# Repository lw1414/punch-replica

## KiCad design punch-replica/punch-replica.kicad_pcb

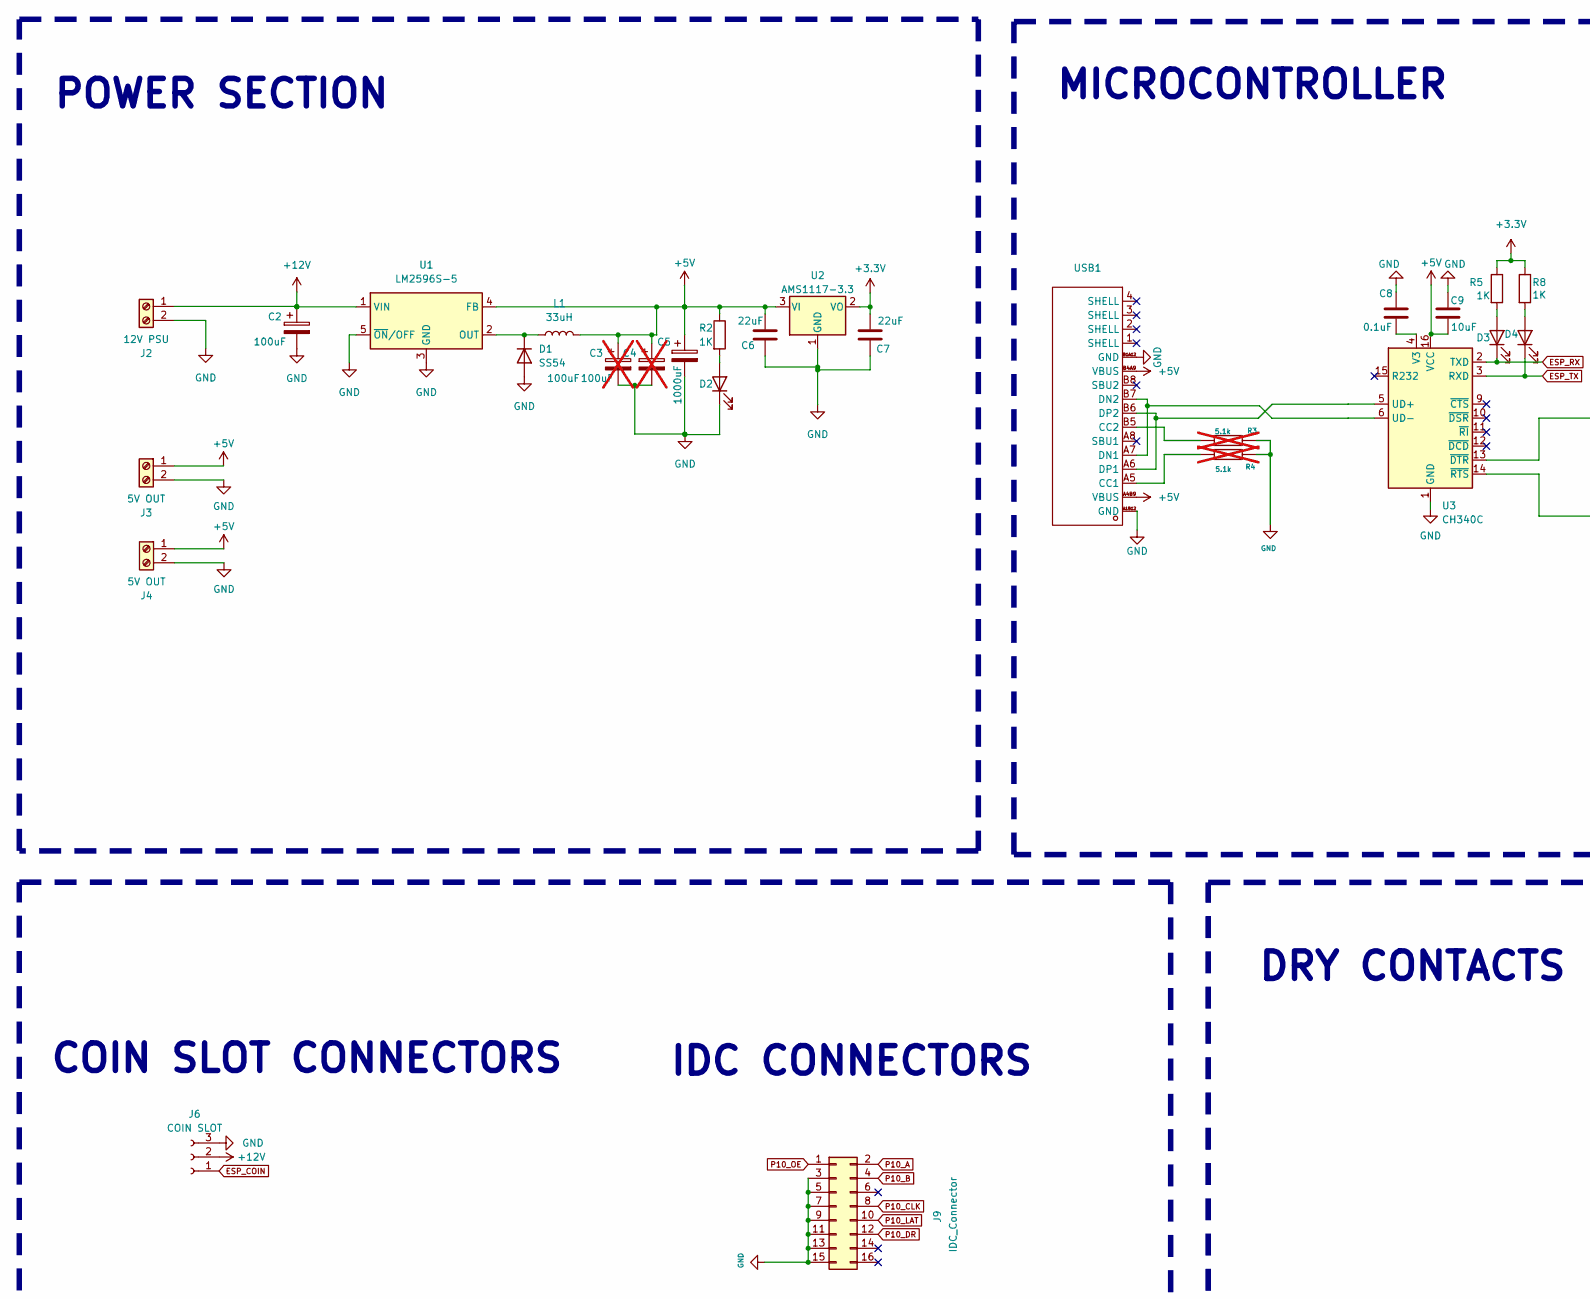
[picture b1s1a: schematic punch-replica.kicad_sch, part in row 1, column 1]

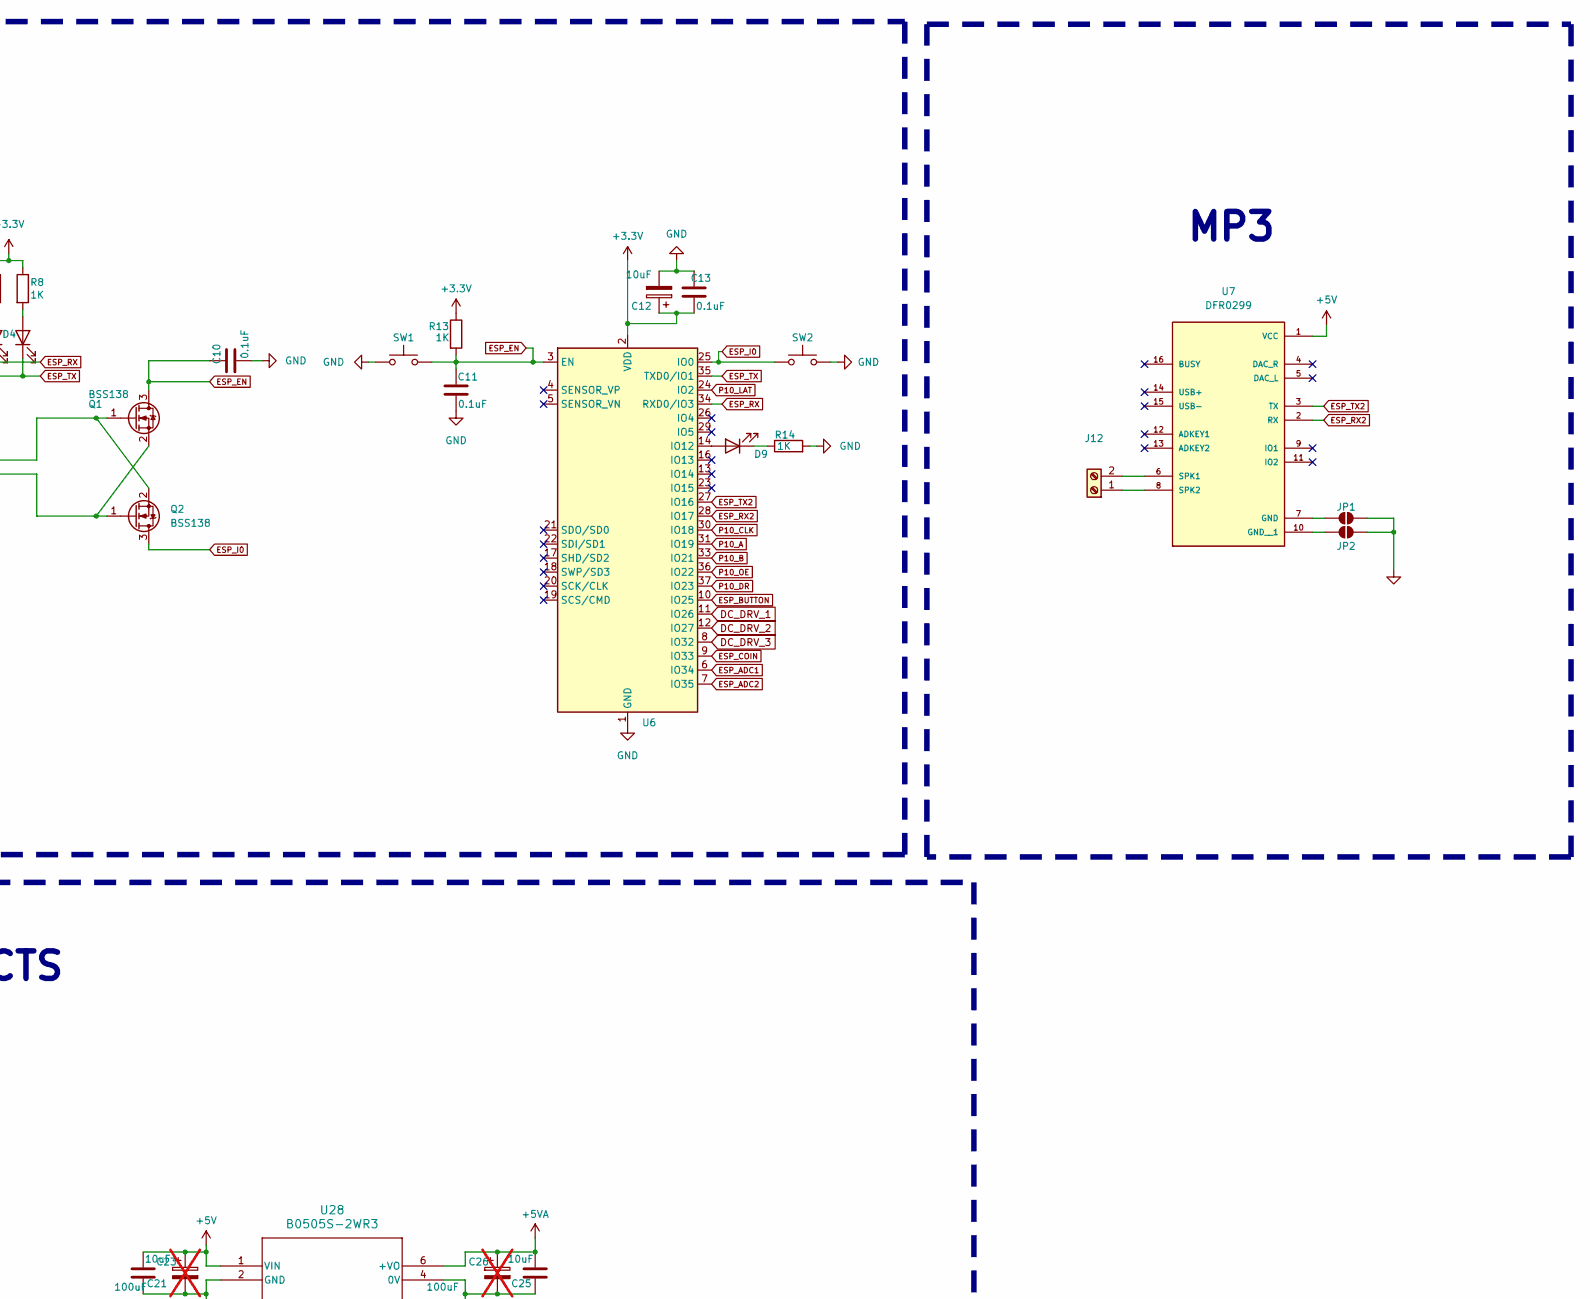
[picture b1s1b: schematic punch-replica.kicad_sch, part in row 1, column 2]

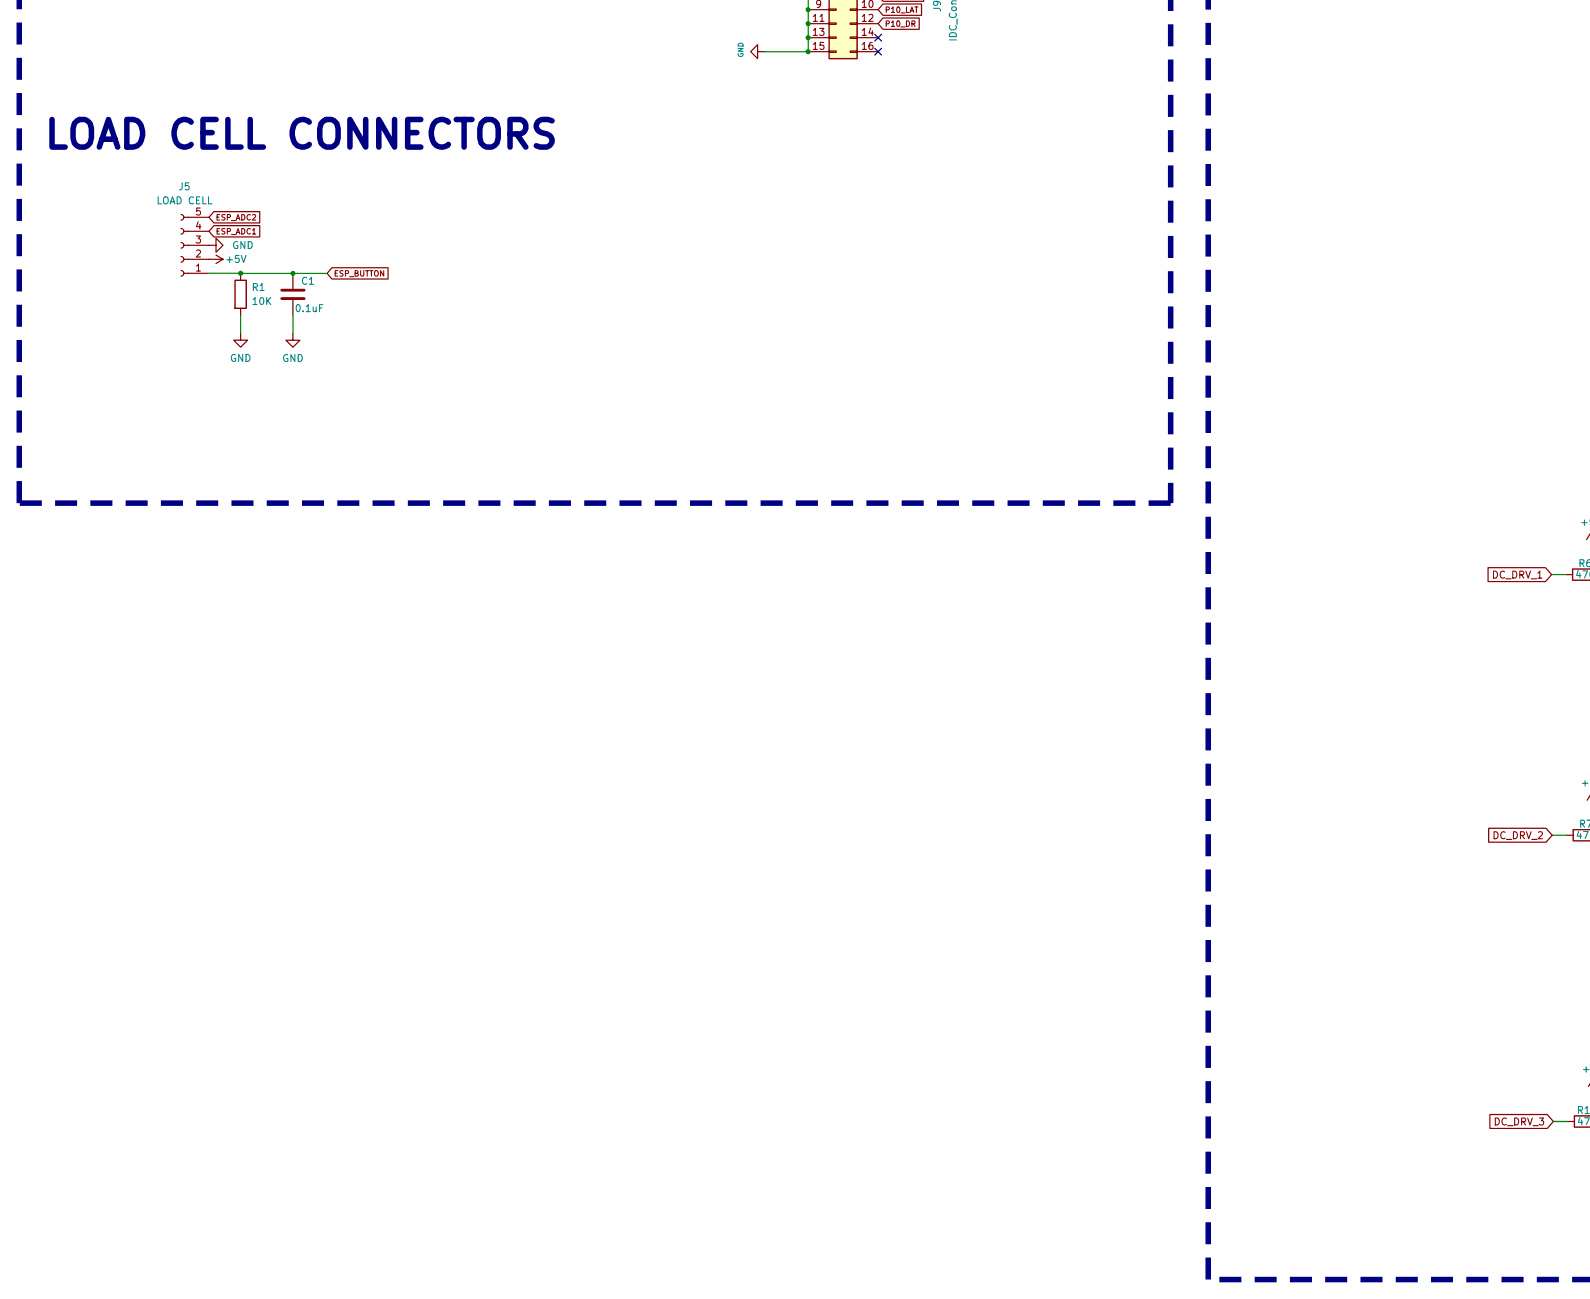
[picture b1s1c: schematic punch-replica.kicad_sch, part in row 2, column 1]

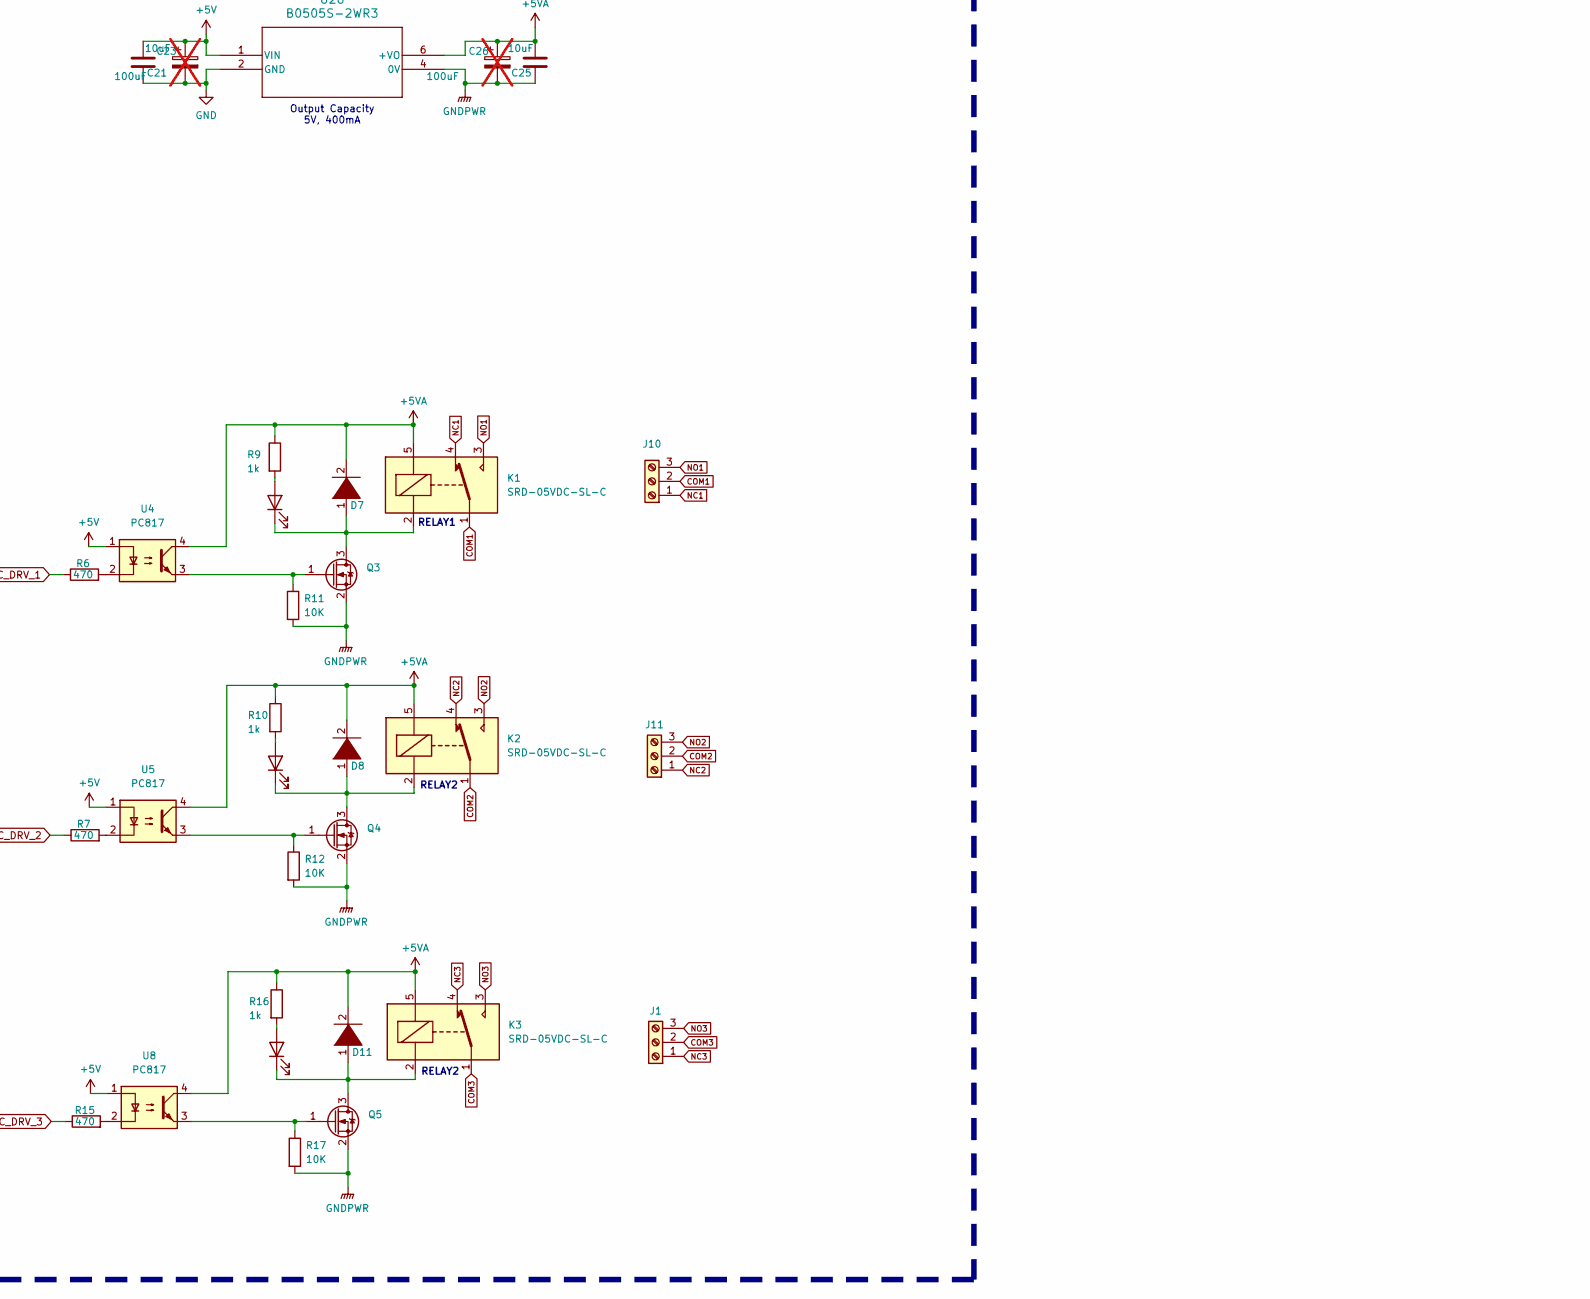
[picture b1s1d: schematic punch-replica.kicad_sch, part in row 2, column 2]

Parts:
C1, C8, C10, C11, C13: 0.1uF; C_0805_2012Metric_Pad1.18x1.45mm_HandSolder; LCSC C49678
C2: 100uF; C_Elec_10x10.2; LCSC C28241
C3, C4, C23, C26: 100uF; C_1210_3225Metric_Pad1.33x2.70mm_HandSolder; LCSC C394395; not fitted
C5: 1000uF; C_Elec_10x10.2; LCSC C189257
C6, C7: 22uF; C_0603_1608Metric; LCSC C59461
C9, C12, C21, C25: 10uF; C_0805_2012Metric_Pad1.18x1.45mm_HandSolder; LCSC C15850
D1: SS54; D_SMA; LCSC C22452
D2, D3, D4, D5, D6, D9, D10: LED; LED_0805_2012Metric_Pad1.15x1.40mm_HandSolder; LCSC C2297
D7, D8, D11: 1N4001; D_SOD-123F; LCSC C2892326
J1, J10, J11: Screw_Terminal_01x03; TerminalBlock_Phoenix_MKDS-1,5-3_1x03_P5.00mm_Horizontal
J2: 12V PSU; TerminalBlock_MaiXu_MX126-5.0-02P_1x02_P5.00mm
J3, J4: 5V OUT; TerminalBlock_MaiXu_MX126-5.0-02P_1x02_P5.00mm
J5: LOAD CELL; TerminalBlock_Phoenix_MKDS-1,5-5-5.08_1x05_P5.08mm_Horizont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
J6: COIN SLOT; TerminalBlock_Phoenix_MKDS-1,5-3_1x03_P5.00mm_Horizontal
J9: IDC_Connector; IDC-TH_16P-P2.54_C3406
J12: Screw_Terminal_01x02; TerminalBlock_MaiXu_MX126-5.0-02P_1x02_P5.00mm
JP1, JP2: SolderJumper_2_Open; SolderJumper-2_P1.3mm_Open_RoundedPad1.0x1.5mm
K1, K2, K3: SRD-05VDC-SL-C; Relay_SPDT_SANYOU_SRD_Series_Form_C; LCSC C35449
L1: 33uH; 470; LCSC C475918
Q1, Q2: BSS138; SOT-23; LCSC C426569
Q3, Q4, Q5: Q_NMOS_Depletion_GSD; SOT-23-3; LCSC C75882
R1, R11, R12, R17: 10K; R_0603_1608Metric_Pad0.98x0.95mm_HandSolder; LCSC C25804
R2, R5, R8, R13, R14: 1K; R_0603_1608Metric_Pad0.98x0.95mm_HandSolder; LCSC C21190
R3, R4: 5.1k; R_0603_1608Metric_Pad0.98x0.95mm_HandSolder; LCSC C103079; not fitted
R6, R7, R15: 470; R_0603_1608Metric_Pad0.98x0.95mm_HandSolder; LCSC C25210
R9, R10, R16: 1k; R_0603_1608Metric_Pad0.98x0.95mm_HandSolder; LCSC C21190
SW1, SW2: SW_Push; SW_Tactile_SPST_NO_Straight_CK_PTS636Sx25SMTRLFS; LCSC C2689642
U1: LM2596S-5; TO-263-5_TabPin3; LCSC C347421
U2: AMS1117-3.3; SOT-223-3_TabPin2; LCSC C5199435
U3: CH340C; SOP-16_3.9x9.9mm_P1.27mm; LCSC C84681
U4, U5, U8: PC817; APC-817xx-SL_AMB; LCSC C66405
U6: ESP32-WROOM-32; ESP32-WROOM-32U; LCSC C529577
U7: DFR0299; MODULE_DFR0299
U28: B0505S-2WR3; B_S-2WR2_MNS; LCSC C5369473
USB1: USB-C-SMD_TYPE-C16PIN; Manufacturer Part TYPE-C16PIN; LCSC Part Name Type-C 母 卧贴

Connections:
+3.3V: C7.2, C12.1, C13.1, R5.1, R8.1, R13.1, U2.2 (VO), U6.2 (VDD)
+5V: C3.1, C4.1, C5.1, C6.2, C9.1, C21.2, C23.1, J3.1, J4.1, J5.2, L1.2, R2.1, U1.4 (FB), U2.3 (VI), U3.16 (VCC), U4.1, U5.1, U7.1 (VCC), U8.1, U28.1 (VIN), USB1.A4B9 (VBUS), USB1.B4A9 (VBUS)
+5VA: C25.2, C26.1, D7.2 (A), D8.2 (A), D11.2 (A), K1.5, K2.5, K3.5, R9.1, R10.1, R16.1, U4.4, U5.4, U8.4, U28.6 (+VO)
+12V: C2.1, J2.1, J6.2, U1.1 (VIN)
COM1: J10.2, K1.1
COM2: J11.2, K2.1
COM3: J1.2, K3.1
DC_DRV_1: R6.1, U6.11 (IO26)
DC_DRV_2: R7.1, U6.12 (IO27)
DC_DRV_3: R15.1, U6.8 (IO32)
ESP_ADC1: J5.4, U6.6 (IO34)
ESP_ADC2: J5.5, U6.7 (IO35)
ESP_BUTTON: C1.2, J5.1, R1.1, U6.10 (IO25)
ESP_COIN: J6.1, U6.9 (IO33)
ESP_EN: C10.2, C11.2, Q1.3 (D), R13.2, SW1.2, U6.3 (EN)
ESP_I0: Q2.3 (D), SW2.1, U6.25 (IO0)
ESP_RX: D3.1 (K), U3.2 (TXD), U6.34 (RXD0/IO3)
ESP_RX2: U6.28 (IO17), U7.2 (RX)
ESP_TX: D4.1 (K), U3.3 (RXD), U6.35 (TXD0/IO1)
ESP_TX2: U6.27 (IO16), U7.3 (TX)
GND: C1.1, C2.2, C3.2, C4.2, C5.2, C6.1, C7.1, C8.2, C9.2, C10.1, C11.1, C12.2, C13.2, C21.1, C23.2, D1.2 (A), D2.1 (K), J2.2, J3.2, J4.2, J5.3, J6.3, J9.3, J9.5, J9.7, J9.9, J9.11, J9.13, J9.15, JP1.2 (B), JP2.2 (B), R1.2, R3.2, R4.2, R14.2, SW1.1, SW2.2, U1.3 (GND), U1.5 (~ON/OFF), U2.1 (GND), U3.1 (GND), U6.1 (GND), U6.15 (GND), U6.38 (GND), U6.39 (GND), U28.2 (GND), USB1.A1B12 (GND), USB1.B1A12 (GND)
GNDPWR: C25.1, C26.2, Q3.2 (S), Q4.2 (S), Q5.2 (S), R11.2, R12.2, R17.2, U28.4 (0V)
NC1: J10.1, K1.4
NC2: J11.1, K2.4
NC3: J1.1, K3.4
NO1: J10.3, K1.3
NO2: J11.3, K2.3
NO3: J1.3, K3.3
unnamed: D1.1 (K), L1.1, U1.2 (OUT)
unnamed: D2.2 (A), R2.2
unnamed: D3.2 (A), R5.2
unnamed: D4.2 (A), R8.2
unnamed: D5.2 (A), R9.2
unnamed: D5.1 (K), D7.1 (K), K1.2, Q3.3 (D)
unnamed: D6.2 (A), R10.2
unnamed: D6.1 (K), D8.1 (K), K2.2, Q4.3 (D)
unnamed: D9.2 (A), U6.14 (IO12)
unnamed: D9.1 (K), R14.1
unnamed: D10.2 (A), R16.2
unnamed: D10.1 (K), D11.1 (K), K3.2, Q5.3 (D)
unnamed: J12.1, U7.8 (SPK2)
unnamed: J12.2, U7.6 (SPK1)
unnamed: JP1.1 (A), U7.7 (GND)
unnamed: JP2.1 (A), U7.10 (GND__1)
unnamed: Q1.1 (G), Q2.2 (S), U3.13 (~DTR)
unnamed: Q1.2 (S), Q2.1 (G), U3.14 (~RTS)
unnamed: Q3.1 (G), R11.1, U4.3
unnamed: Q4.1 (G), R12.1, U5.3
unnamed: Q5.1 (G), R17.1, U8.3
unnamed: R6.2, U4.2
unnamed: R7.2, U5.2
unnamed: R15.2, U8.2
unnamed: U3.5 (UD+), USB1.A6 (DP1), USB1.B6 (DP2)
unnamed: U3.6 (UD-), USB1.A7 (DN1), USB1.B7 (DN2)
unnamed: C8.1, U3.4 (V3)
unnamed: R4.1, USB1.A5 (CC1)
unnamed: R3.1, USB1.B5 (CC2)
P10_A: J9.2, U6.31 (IO19)
P10_B: J9.4, U6.33 (IO21)
P10_CLK: J9.8, U6.30 (IO18)
P10_DR: J9.12, U6.37 (IO23)
P10_LAT: J9.10, U6.24 (IO2)
P10_OE: J9.1, U6.36 (IO22)

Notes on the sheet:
Output Capacity 5V, 400mA
MICROCONTROLLER
MP3
DRY CONTACTS
RELAY2
RELAY1
POWER SECTION
LOAD CELL CONNECTORS
IDC CONNECTORS
COIN SLOT CONNECTORS

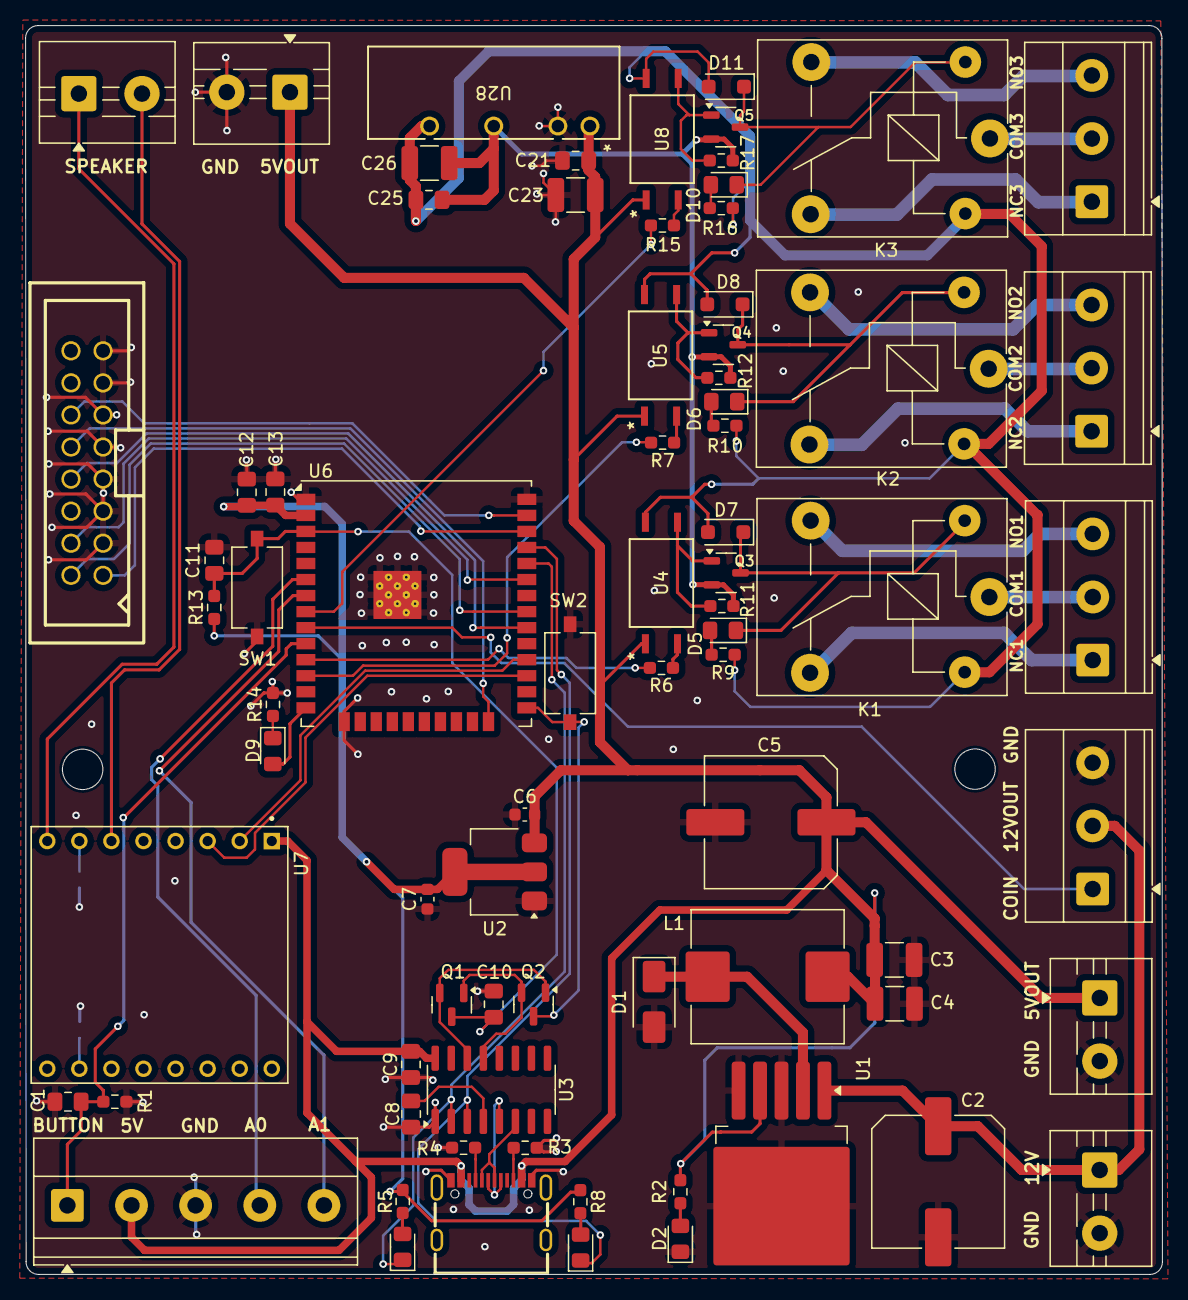
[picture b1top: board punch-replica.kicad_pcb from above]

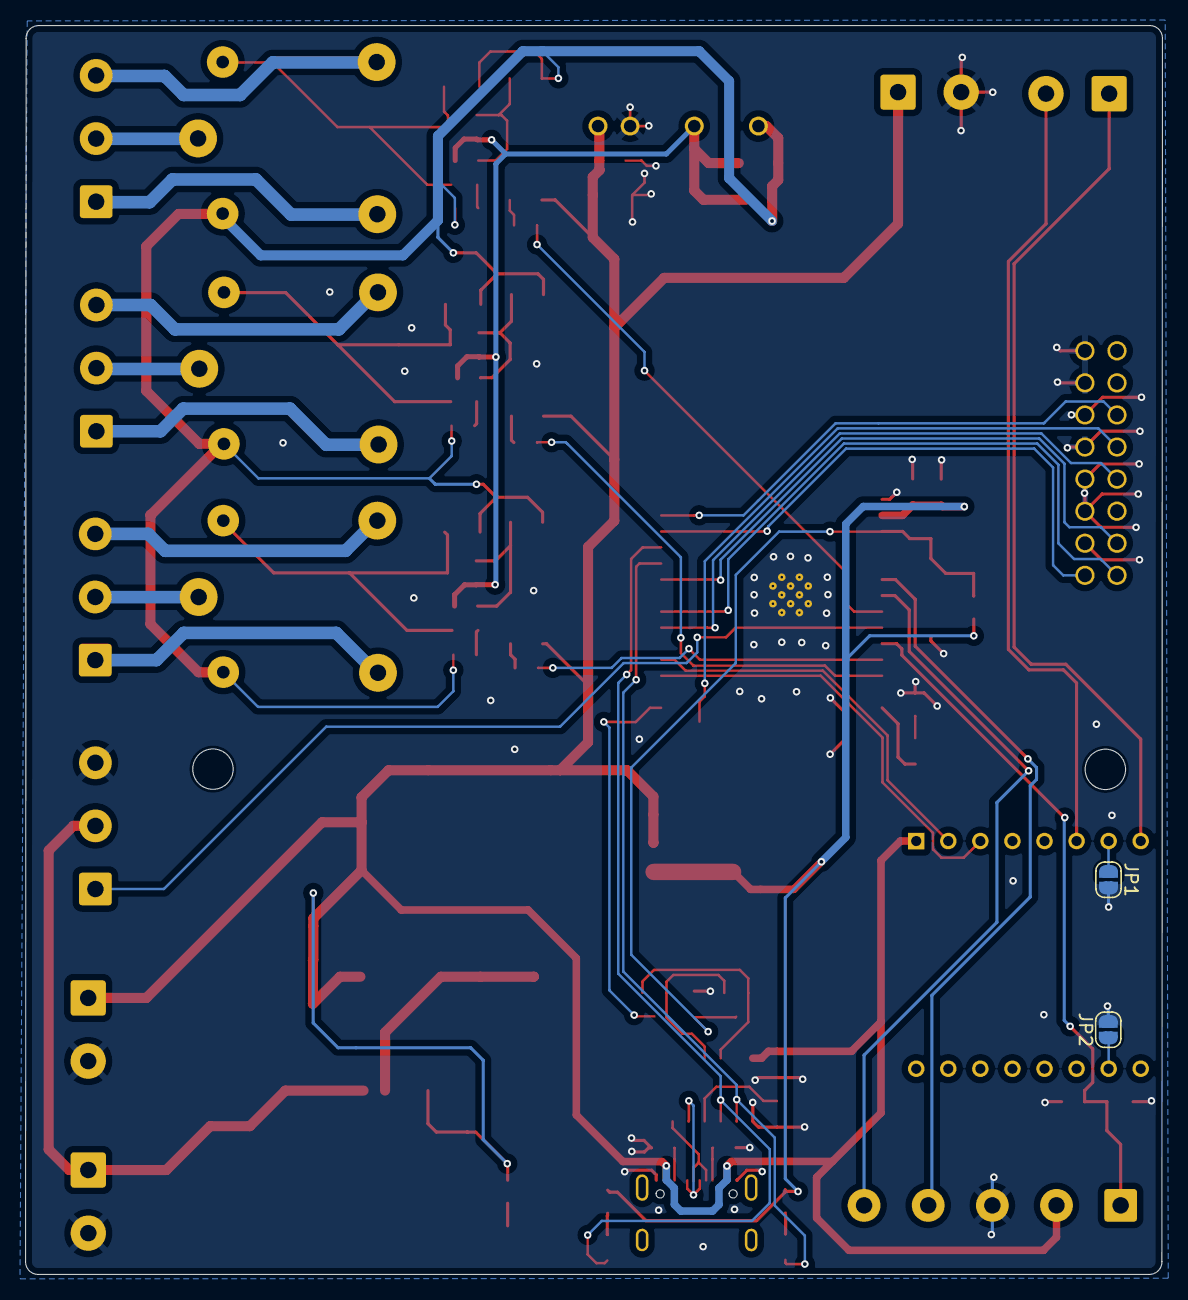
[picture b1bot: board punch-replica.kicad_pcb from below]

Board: 2 copper layers, 90.0 x 98.9 mm, 78 parts (2 on the bottom side), 63 nets.

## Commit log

2026-02-11 pcb parts placement
2026-03-03 - adjustment
2026-04-15 -update
2026-04-21 -
    -add punch code whole process
    -done idle state lcd
    -lacking fix on lcd
    -lacking scoring system
2026-05-07 -video guide and pdf
